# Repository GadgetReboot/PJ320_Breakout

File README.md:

# PJ320_Breakout
<br><br><BR><BR>
PJ320 breakout board for 3.5mm TRRS jacks<BR><BR>
Allows using SMD PJ320D or Through Hole PJ320A jacks on a breadboard or with Dupont wires

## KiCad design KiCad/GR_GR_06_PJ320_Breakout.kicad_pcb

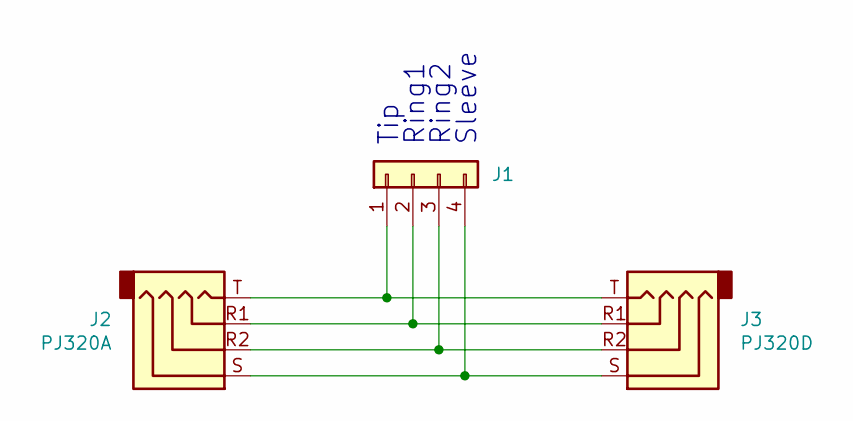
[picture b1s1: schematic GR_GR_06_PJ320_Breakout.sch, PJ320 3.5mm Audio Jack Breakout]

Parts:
J1: Conn_01x04; PinHeader_1x04_P2.54mm_Vertical
J2: PJ320A
J3: PJ320D

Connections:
unnamed: J1.1, J2.T, J3.T
unnamed: J1.2, J2.R1, J3.R1
unnamed: J1.3, J2.R2, J3.R2
unnamed: J1.4, J2.S, J3.S

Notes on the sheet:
Tip
Ring1
Ring2
Sleeve

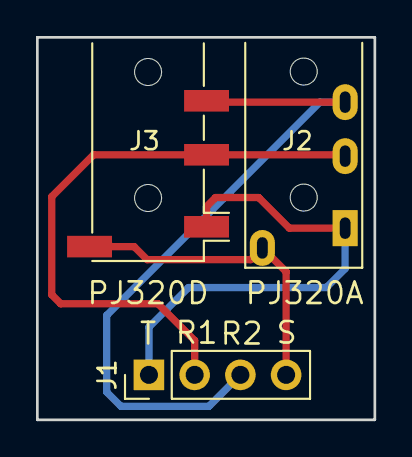
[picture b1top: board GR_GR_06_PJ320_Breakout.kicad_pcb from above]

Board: 2 copper layers, 18.8 x 21.2 mm, 3 parts (0 on the bottom side), 4 nets.
